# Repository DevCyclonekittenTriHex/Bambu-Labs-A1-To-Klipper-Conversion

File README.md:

## Bambu Lab A1 Klipper Conversion (In development)

## Join Chaz's [**Discord Server**](https://discord.gg/W6B5mBejuC) to help with all bambu labs klipper mods.

> [!Caution]
> Doing any modifications may void your warrenty! 
> [!Caution]
> This Project is in currently not finished, this conversion is done fully at your own risk, I am not liable for any damages done to your machine.

This is constantly being updated, the docs for the conversion will be [Here!](https://devcyclonekittentrihex.github.io/A1K-Documentation/Docs/)

# Aim
The aim of this open source project is to create drop in circuit boards for the Bambu Labs A1 and A1 mini machines; and to provide a good framework to promote modding of these machines. This project will try to intergrate every part from the original printer to make the upgrade seamless. This will give back people privacy and a fully lan or offline system to print.

Currently, I have designed the a1 mainboard and a1/a1m toolhead boards, and am currently going through revisioning.
My target for the pcbs are to order them by November 30th

# Functions

Does work:
- Full hotend heating 
- XYZ Movement
- Stock Part Cooling Fans
- Auto Bed Levelling (with biqu microprobe)
- Filament Runout (with biqu sfs2)

Does not work:
- Heated Bed : Currently have the pinout for it, will be implemented in pcbs.
- Filament Sensor : It is a linear hall sensor, pinout unknown. Will attempt to find.
- AMS Lite : Closed source, other open mmus are compatible
- Display : An unidentified display that is possibly using 4SPI

# Previous Experiments
I previously hooked up an skr pico to the printer, and got it printing without a heated bed. Here is the footage. I also killed my mainboard so there is no more footage.
https://youtu.be/fLf-GMceLxE

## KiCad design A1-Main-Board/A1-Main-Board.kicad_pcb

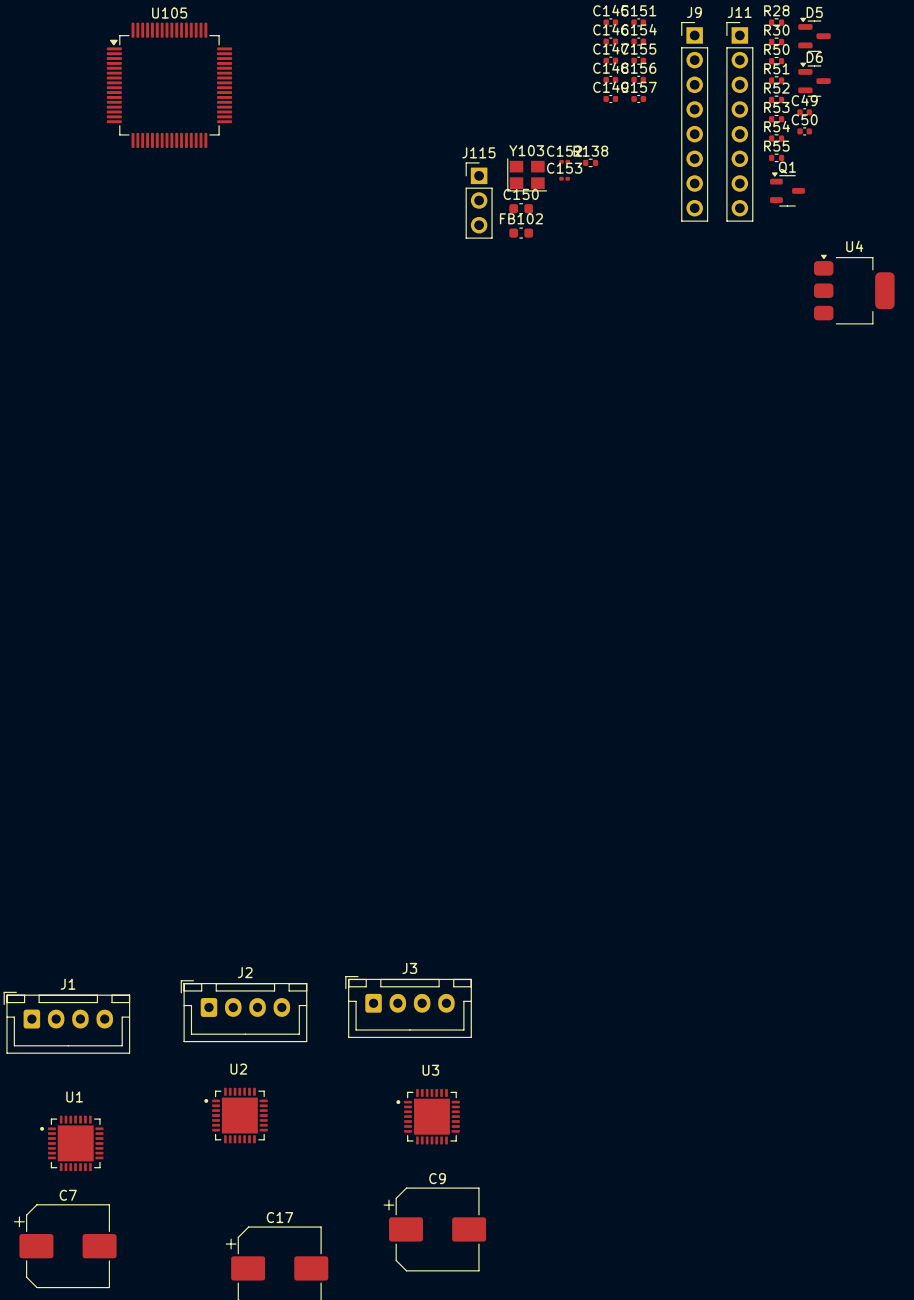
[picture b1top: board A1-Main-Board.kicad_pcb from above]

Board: 2 copper layers, 43 parts (0 on the bottom side), 33 nets, no tracks yet.

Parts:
C7, C9, C17: 100uF; CP_Elec_8x10
C49, C50, C147, C148, C149, C154, C155, C156, C157: 100nF; C_0402_1005Metric
C145, C146: 30pF; C_0402_1005Metric
C150: 10uF; C_0603_1608Metric
C151: 10nF; C_0402_1005Metric
C152, C153: 1uF; C_0201_0603Metric
D5, D6: BAV99; SOT-23
FB102: 120r 100MHz; C_0603_1608Metric
J1, J2, J3: MotorJST; JST_XH_B4B-XH-A_1x04_P2.50mm_Vertical
J9: FPC1; PinHeader_1x08_P2.54mm_Vertical
J11: FPC2; PinHeader_1x08_P2.54mm_Vertical
J115: BOOT; PinHeader_1x03_P2.54mm_Vertical
Q1: NMOS; SOT-23-3
R28: 10R; R_0402_1005Metric
R30: 20kR; R_0402_1005Metric
R50, R53: 4.7kR; R_0402_1005Metric
R51, R52, R54, R55: 2.37kR; R_0402_1005Metric
R138: 10kR; R_0402_1005Metric
U1, U2, U3: TMC2209-LA
U4: AMS1117-3.3; SOT-223-3_TabPin2
U105: STM32G431RBT3; LQFP-64_10x10mm_P0.5mm
Y103: Crystal_GND24; Crystal_SMD_3225-4Pin_3.2x2.5mm

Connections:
+3V3: C147.1, C149.1, C150.1, C153.1, C154.1, C155.1, C156.1, C157.1, FB102.2, J115.1, U1.15 (VCC_IO), U2.9 (MS1_AD0), U2.15 (VCC_IO), U3.10 (MS2_AD1), U3.15 (VCC_IO), U105.1 (VBAT), U105.16 (VDD), U105.32 (VDD), U105.48 (VDD), U105.64 (VDD)
+3V3A: C151.1, C152.1, D5.2 (A), D6.2 (A), FB102.1, R50.1, R53.1, U105.28 (VREF+), U105.29 (VDDA)
+5V: J11.1, U1.8 (5VOUT), U2.8 (5VOUT), U3.8 (5VOUT)
+24V: C7.1, C9.1, C17.1, U1.22 (VS), U1.28 (VS), U2.22 (VS), U2.28 (VS), U3.22 (VS), U3.28 (VS)
/drivers/MA_UART: U1.14 (~PD_UART), U2.14 (~PD_UART), U3.14 (~PD_UART), U105.22 (PC4)
/heated-bed/10k_THB_INP: J11.4, R53.2, R54.1
/heated-bed/100k_THB_INP: J11.2, R50.2, R51.1
/heated-bed/BED_THERM_1: C49.1, R52.2, U105.36 (PB14)
/heated-bed/BED_THERM_2: C50.1, R55.2, U105.43 (PA9)
/heated-bed/HEATED_BED-: J11.7, Q1.1 (D)
/heated-bed/HEATED_BED_PWM: R28.1, R30.1, U105.38 (PC6)
GND: C7.2, C9.2, C17.2, C49.2, C50.2, C145.2, C146.2, C148.2, C151.2, C152.2, C153.2, D5.1 (K), D6.1 (K), J11.3, J11.5, J11.8, J115.3, Q1.3 (S), R30.2, U1.3 (GND), U1.9 (MS1_AD0), U1.10 (MS2_AD1), U1.18 (GND), U1.29 (EXP), U2.3 (GND), U2.10 (MS2_AD1), U2.18 (GND), U2.29 (EXP), U3.3 (GND), U3.9 (MS1_AD0), U3.18 (GND), U3.29 (EXP), U105.15 (VSS), U105.27 (VSSA), U105.31 (VSS), U105.47 (VSS), U105.63 (VSS), Y103.2, Y103.4
unnamed: C147.2, C149.2, C150.2, C154.2, C155.2, C156.2, C157.2
unnamed: D5.3 (K), R51.2, R52.1
unnamed: D6.3 (K), R54.2, R55.1
unnamed: J1.1, U1.24 (OA1)
unnamed: J1.2, U1.26 (OB1)
unnamed: J1.3, U1.21 (OA2)
unnamed: J1.4, U1.1 (OB2)
unnamed: J2.1, U2.24 (OA1)
unnamed: J2.2, U2.26 (OB1)
unnamed: J2.3, U2.21 (OA2)
unnamed: J2.4, U2.1 (OB2)
unnamed: J3.1, U3.24 (OA1)
unnamed: J3.2, U3.26 (OB1)
unnamed: J3.3, U3.21 (OA2)
unnamed: J3.4, U3.1 (OB2)
unnamed: J115.2, R138.1
unnamed: Q1.2 (G), R28.2
unnamed: C148.1, U105.7 (PG10)
unnamed: R138.2, U105.61 (PB8)
unnamed: C145.1, U105.5 (PF0), Y103.1
unnamed: C146.1, U105.6 (PF1), Y103.3

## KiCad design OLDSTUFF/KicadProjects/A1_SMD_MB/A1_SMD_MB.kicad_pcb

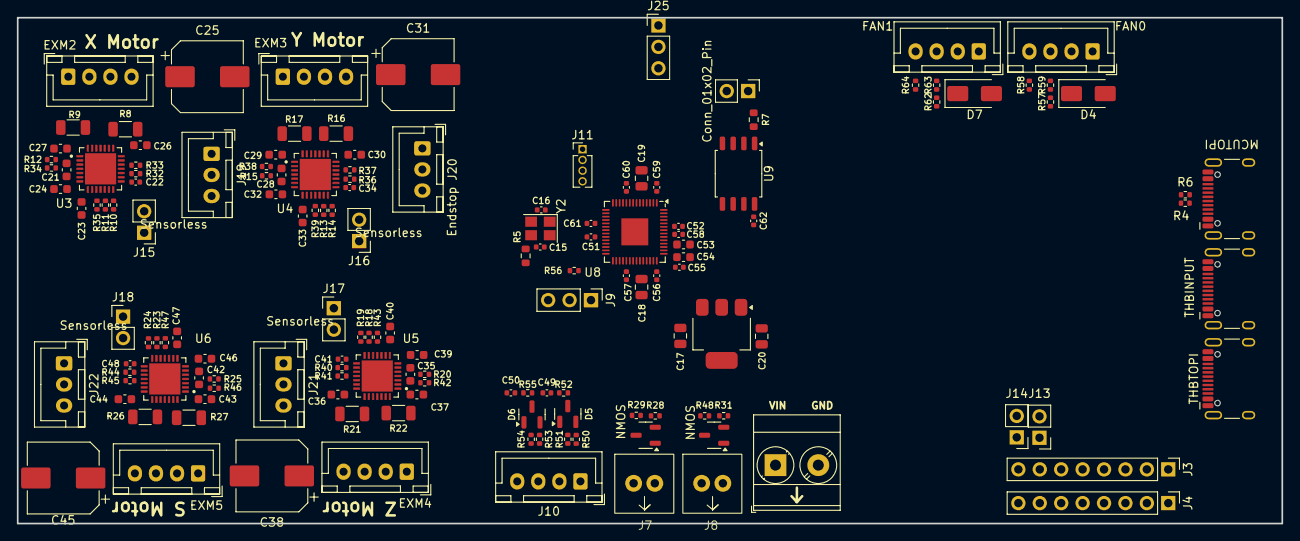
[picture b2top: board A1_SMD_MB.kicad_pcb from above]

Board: 2 copper layers, 150.0 x 60.0 mm, 148 parts (0 on the bottom side), 134 nets, no tracks yet.

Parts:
C15, C16: 15pF; C_0402_1005Metric
C17, C18, C19, C20: 10uF; C_0805_2012Metric
C21, C28, C35, C42: 22nF 50V; C_0603_1608Metric
C22, C34, C41, C48, C49, C50, C51, C52, C55, C56, C57, C58, C59, C60, C61, C62: 100nF; C_0402_1005Metric
C23, C33, C40, C47: 4.7uF; C_0603_1608Metric
C24, C26, C27, C29, C30, C32, C36, C37, C39, C43, C44, C46: 100nF 50V; C_0603_1608Metric
C25, C31, C38, C45: 100uF; CP_Elec_8x10
C53, C54: 1uF; C_0603_1608Metric
D4, D7: D; D_SMA
D5, D6: BAV99; SOT-23
EXM2, EXM3, EXM4, EXM5: Conn_01x04; JST_XH_B4B-XH-A_1x04_P2.50mm_Vertical
J3: FPC2; PinHeader_1x08_P2.54mm_Vertical
J4: FPC1; PinHeader_1x08_P2.54mm_Vertical
J6: FAN0; JST_XH_B4B-XH-A_1x04_P2.50mm_Vertical
J7: HE; ScrewTerminal 7mm x 7mm
J8: HB; ScrewTerminal 7mm x 7mm
J9: Conn_01x03_Pin; PinHeader_1x03_P2.54mm_Vertical
J10: BedTherms; JST_XH_B4B-XH-A_1x04_P2.50mm_Vertical
J11: SWD; PinHeader_1x04_P1.27mm_Vertical
J12: Conn_01x02_Pin; PinHeader_1x02_P2.54mm_Vertical
J13: THM2JMP; PinHeader_1x02_P2.54mm_Vertical
J14: THM1JMP; PinHeader_1x02_P2.54mm_Vertical
J15, J16, J17, J18: Sensorless; PinHeader_1x02_P2.54mm_Vertical
J19, J20, J21, J22: Endstop; JST_XH_B3B-XH-A_1x03_P2.50mm_Vertical
J23: PWR; 1x2 Terminal Block
J24: FAN1; JST_XH_B4B-XH-A_1x04_P2.50mm_Vertical
J25: SPR_IO; PinHeader_1x03_P2.54mm_Vertical
P1: MCUTOPI; USB_C_Receptacle_HCTL_HC-TYPE-C-16P-01A
P2: THBINPUT; USB_C_Receptacle_HCTL_HC-TYPE-C-16P-01A
P3: THBTOPI; USB_C_Receptacle_HCTL_HC-TYPE-C-16P-01A
Q1, Q2: NMOS; SOT-23-3
R4, R6: 27.4o; R_0402_1005Metric
R5: 1k; R_0603_1608Metric
R7: 1ko; R_0603_1608Metric
R8, R9, R16, R17, R21, R22, R26, R27: 100mΩ; R_1206_3216Metric
R10, R11, R12, R13, R14, R15, R18, R19, R20, R23, R24, R25: 20kΩ; R_0402_1005Metric
R28, R31: 10R; R_0402_1005Metric
R29, R48, R58, R64: 20kR; R_0402_1005Metric
R32, R33, R34, R35, R36, R37, R38, R39, R40, R41, R42, R43, R44, R45, R46, R47: 100o; R_0402_1005Metric
R50, R53: 4.7kR; R_0402_1005Metric
R51, R52, R54, R55: 2.37kR; R_0402_1005Metric
R56: 10k; R_0402_1005Metric
R57, R59, R62, R63: 100R; R_0402_1005Metric
U3, U4, U5, U6: TMC2209-LA
U7: NCP1117-1.5_SOT223; SOT-223-3_TabPin2
U8: RP2040; QFN-56-1EP_7x7mm_P0.4mm_EP3.2x3.2mm
U9: W25Q128JVS; SOIC-8_5.3x5.3mm_P1.27mm
Y2: ABM8-272-T3; Crystal_SMD_Abracon_ABM8AIG-4Pin_3.2x2.5mm

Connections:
+1V1: C51.1, C52.1, C53.1, U8.23 (DVDD), U8.45 (VREG_VOUT), U8.50 (DVDD)
+3.3VADC: D5.2 (A), D6.2 (A), R50.1, R53.1
+3V3: C18.1, C19.1, C20.1, C22.2, C34.2, C41.2, C48.2, C54.1, C55.1, C56.1, C57.1, C58.1, C59.1, C60.1, C61.1, C62.1, J3.5, J9.1, J11.1, R12.1, R15.1, R20.1, R25.1, U3.15 (VCC_IO), U4.9 (MS1_AD0), U4.15 (VCC_IO), U5.10 (MS2_AD1), U5.15 (VCC_IO), U6.9 (MS1_AD0), U6.10 (MS2_AD1), U6.15 (VCC_IO), U7.2 (VO), U8.1 (IOVDD), U8.10 (IOVDD), U8.22 (IOVDD), U8.33 (IOVDD), U8.42 (IOVDD), U8.43 (ADC_AVDD), U8.44 (VREG_IN), U8.48 (USB_VDD), U8.49 (IOVDD), U9.8 (VCC)
+5V: C23.2, C33.2, C40.2, C47.2, J3.1, J3.2, J19.3, J20.3, J21.3, J22.3, P2.A8 (SBU1), P2.B8 (SBU2), U3.8 (5VOUT), U4.8 (5VOUT), U5.8 (5VOUT), U6.8 (5VOUT)
+24V: C24.1, C25.1, C26.2, C27.2, C29.2, C30.2, C31.1, C32.1, C36.2, C37.2, C38.1, C39.1, C43.2, C44.2, C45.1, C46.1, D4.2 (A), D7.2 (A), J6.1, J7.1, J8.1, J23.1, J24.1, P2.A4 (VBUS), P2.A9 (VBUS), P2.B4 (VBUS), P2.B9 (VBUS), U3.22 (VS), U3.28 (VS), U4.22 (VS), U4.28 (VS), U5.22 (VS), U5.28 (VS), U6.22 (VS), U6.28 (VS)
/Motors/MS_DIAG: J22.1, R47.2, U8.34 (GPIO22)
/Motors/MS_DIR: R45.1, U8.32 (GPIO21)
/Motors/MS_EN: R46.1, U8.30 (GPIO19)
/Motors/MS_STEP: R44.1, U8.31 (GPIO20)
/Motors/MX_DIAG: J19.1, R35.2, U8.13 (GPIO10)
/Motors/MX_DIR: R33.1, U8.12 (GPIO9)
/Motors/MX_EN: R34.1, U8.9 (GPIO7)
/Motors/MX_STEP: R32.1, U8.11 (GPIO8)
/Motors/MY_DIAG: J20.1, R39.2, U8.17 (GPIO14)
/Motors/MY_DIR: R37.1, U8.16 (GPIO13)
/Motors/MY_EN: R38.1, U8.14 (GPIO11)
/Motors/MY_STEP: R36.1, U8.15 (GPIO12)
/Motors/MZ_DIAG: J21.1, R43.2, U8.29 (GPIO18)
/Motors/MZ_DIR: R41.1, U8.28 (GPIO17)
/Motors/MZ_EN: R42.1, U8.18 (GPIO15)
/Motors/MZ_STEP: R40.1, U8.27 (GPIO16)
/Motors/UART: R10.2, R14.2, R19.2, R24.2, U3.14 (~PD_UART), U4.14 (~PD_UART), U5.14 (~PD_UART), U6.14 (~PD_UART), U8.8 (GPIO6)
/fpc/HB_CT: J3.6, U8.6 (GPIO4)
/fpc/THM1: C50.1, J14.2, R55.2, U8.41 (GPIO29_ADC3)
/fpc/THM2: C49.1, J13.2, R52.2, U8.40 (GPIO28_ADC2)
/mcu/G1: R58.1, U8.3 (GPIO1)
/mcu/G2: R31.1, R48.1, U8.4 (GPIO2)
/mcu/G3: R28.1, R29.1, U8.5 (GPIO3)
/mcu/G23: J25.1, U8.35 (GPIO23)
/mcu/G24: J25.2, U8.36 (GPIO24)
/mcu/G25: J25.3, U8.37 (GPIO25)
/mcu/G26: R62.1, U8.38 (GPIO26_ADC0)
/mcu/G27: R64.1, U8.39 (GPIO27_ADC1)
/mcu/GPIO0: R57.1, U8.2 (GPIO0)
/mcu/IO0: U8.53 (QSPI_SD0), U9.5 (DI/IO_{0})
/mcu/IO1: U8.55 (QSPI_SD1), U9.2 (DO/IO_{1})
/mcu/IO2: U8.54 (QSPI_SD2), U9.3 (~WP/IO_{2})
/mcu/IO3: U8.51 (QSPI_SD3), U9.7 (~HOLD/~RESET/IO_{3})
/mcu/IO_CLK: U8.52 (QSPI_SCLK), U9.6 (CLK)
/mcu/IO_CS: R7.2, U8.56 (QSPI_SS), U9.1 (~CS)
/mcu/USB_D+: P1.A6 (D+), R4.1
/mcu/USB_D-: P1.A7 (D-), R6.1
/mcu/XIN: C16.2, U8.20 (XIN), Y2.1
/mcu/XOUT: R5.2, U8.21 (XOUT)
/stuff/HB_S: Q2.2 (G), R31.2
/stuff/HE_S: Q1.2 (G), R28.2
GND: C22.1, C23.1, C25.2, C26.1, C27.1, C29.1, C30.1, C31.2, C33.1, C34.1, C36.1, C37.1, C38.2, C40.1, C41.1, C43.1, C44.1, C45.2, C47.1, C48.1, C49.2, C50.2, D4.1 (K), D5.1 (K), D6.1 (K), D7.1 (K), J3.3, J3.4, J6.2, J10.2, J10.4, J19.2, J20.2, J21.2, J22.2, J23.2, J24.2, P1.A1 (GND), P1.A12 (GND), P1.B1 (GND), P1.B12 (GND), P1.S1 (SHIELD), P2.A1 (GND), P2.A12 (GND), P2.B1 (GND), P2.B12 (GND), P2.S1 (SHIELD), P3.A1 (GND), P3.A12 (GND), P3.B1 (GND), P3.B12 (GND), P3.S1 (SHIELD), Q1.3 (S), Q2.3 (S), R8.2, R9.2, R10.1, R11.1, R13.1, R14.1, R16.2, R17.2, R18.1, R19.1, R21.2, R22.2, R23.1, R24.1, R26.2, R27.2, R29.2, R48.2, U3.3 (GND), U3.9 (MS1_AD0), U3.10 (MS2_AD1), U3.18 (GND), U3.29 (EXP), U4.3 (GND), U4.10 (MS2_AD1), U4.18 (GND), U4.29 (EXP), U5.3 (GND), U5.9 (MS1_AD0), U5.18 (GND), U5.29 (EXP), U6.3 (GND), U6.18 (GND), U6.29 (EXP)
GND3: C15.1, C16.1, C17.2, C18.2, C19.2, C20.2, C51.2, C52.2, C53.2, C54.2, C55.2, C56.2, C57.2, C58.2, C59.2, C60.2, C61.2, C62.2, J9.3, J11.4, J12.2, U7.1 (GND), U8.19 (TESTEN), U8.57 (GND), U9.4 (GND), Y2.2, Y2.4
unnamed: C15.2, R5.1, Y2.3
unnamed: D5.3 (K), R51.2, R52.1
unnamed: D6.3 (K), R54.2, R55.1
unnamed: EXM2.1, U3.1 (OB2)
unnamed: EXM2.2, U3.26 (OB1)
unnamed: EXM2.3, U3.24 (OA1)
unnamed: EXM2.4, U3.21 (OA2)
unnamed: EXM3.1, U4.1 (OB2)
unnamed: EXM3.2, U4.26 (OB1)
unnamed: EXM3.3, U4.24 (OA1)
unnamed: EXM3.4, U4.21 (OA2)
unnamed: EXM4.1, U5.1 (OB2)
unnamed: EXM4.2, U5.26 (OB1)
unnamed: EXM4.3, U5.24 (OA1)
unnamed: EXM4.4, U5.21 (OA2)
unnamed: EXM5.1, U6.1 (OB2)
unnamed: EXM5.2, U6.26 (OB1)
unnamed: EXM5.3, U6.24 (OA1)
unnamed: EXM5.4, U6.21 (OA2)
unnamed: J6.3, R59.2
unnamed: J6.4, R58.2
unnamed: J7.2, Q1.1 (D)
unnamed: J8.2, Q2.1 (D)
unnamed: J9.2, R56.1
unnamed: J10.1, R50.2, R51.1
unnamed: J10.3, R53.2, R54.1
unnamed: J11.2, U8.24 (SWCLK)
unnamed: J11.3, U8.25 (SWD)
unnamed: J12.1, R7.1
unnamed: J3.7, J13.1
unnamed: J3.8, J14.1
unnamed: J15.1, R35.1
unnamed: J15.2, U3.11 (DIAG)
unnamed: J16.1, R39.1
unnamed: J16.2, U4.11 (DIAG)
unnamed: J17.1, R43.1
unnamed: J17.2, U5.11 (DIAG)
unnamed: J18.1, R47.1
unnamed: J18.2, U6.11 (DIAG)
unnamed: J24.3, R63.2
unnamed: J24.4, R64.2
unnamed: P2.A5 (CC), P2.B5 (VCONN)
unnamed: P2.A6 (D+), P3.A6 (D+)
unnamed: P2.A7 (D-), P3.A7 (D-)
unnamed: R57.2, R59.1
unnamed: R62.2, R63.1
unnamed: R8.1, U3.23 (BRA)
unnamed: R9.1, U3.27 (BRB)
unnamed: R11.2, U3.13 (CLK)
unnamed: C21.1, U3.5 (CPI)
unnamed: C21.2, U3.4 (CPO)
unnamed: R33.2, U3.19 (DIR)
unnamed: R32.2, U3.16 (STEP)
unnamed: C24.2, U3.6 (VCP)
unnamed: R12.2, R34.2, U3.2 (~EN)
unnamed: R16.1, U4.23 (BRA)
unnamed: R17.1, U4.27 (BRB)
unnamed: R13.2, U4.13 (CLK)
unnamed: C28.1, U4.5 (CPI)
unnamed: C28.2, U4.4 (CPO)
unnamed: R37.2, U4.19 (DIR)
unnamed: R36.2, U4.16 (STEP)
unnamed: C32.2, U4.6 (VCP)
unnamed: R15.2, R38.2, U4.2 (~EN)
unnamed: R21.1, U5.23 (BRA)
unnamed: R22.1, U5.27 (BRB)
unnamed: R18.2, U5.13 (CLK)
unnamed: C35.1, U5.5 (CPI)
unnamed: C35.2, U5.4 (CPO)
unnamed: R41.2, U5.19 (DIR)
unnamed: R40.2, U5.16 (STEP)
unnamed: C39.2, U5.6 (VCP)
unnamed: R20.2, R42.2, U5.2 (~EN)
unnamed: R26.1, U6.23 (BRA)
unnamed: R27.1, U6.27 (BRB)
unnamed: R23.2, U6.13 (CLK)
unnamed: C42.1, U6.5 (CPI)
unnamed: C42.2, U6.4 (CPO)
unnamed: R45.2, U6.19 (DIR)
unnamed: R44.2, U6.16 (STEP)
unnamed: C46.2, U6.6 (VCP)
unnamed: R25.2, R46.2, U6.2 (~EN)
unnamed: R56.2, U8.26 (RUN)
unnamed: R6.2, U8.46 (USB_DM)
unnamed: R4.2, U8.47 (USB_DP)
VBUS: C17.1, P1.A4 (VBUS), P1.A9 (VBUS), P1.B4 (VBUS), P1.B9 (VBUS), P3.A4 (VBUS), P3.A9 (VBUS), P3.B4 (VBUS), P3.B9 (VBUS), U7.3 (VI)

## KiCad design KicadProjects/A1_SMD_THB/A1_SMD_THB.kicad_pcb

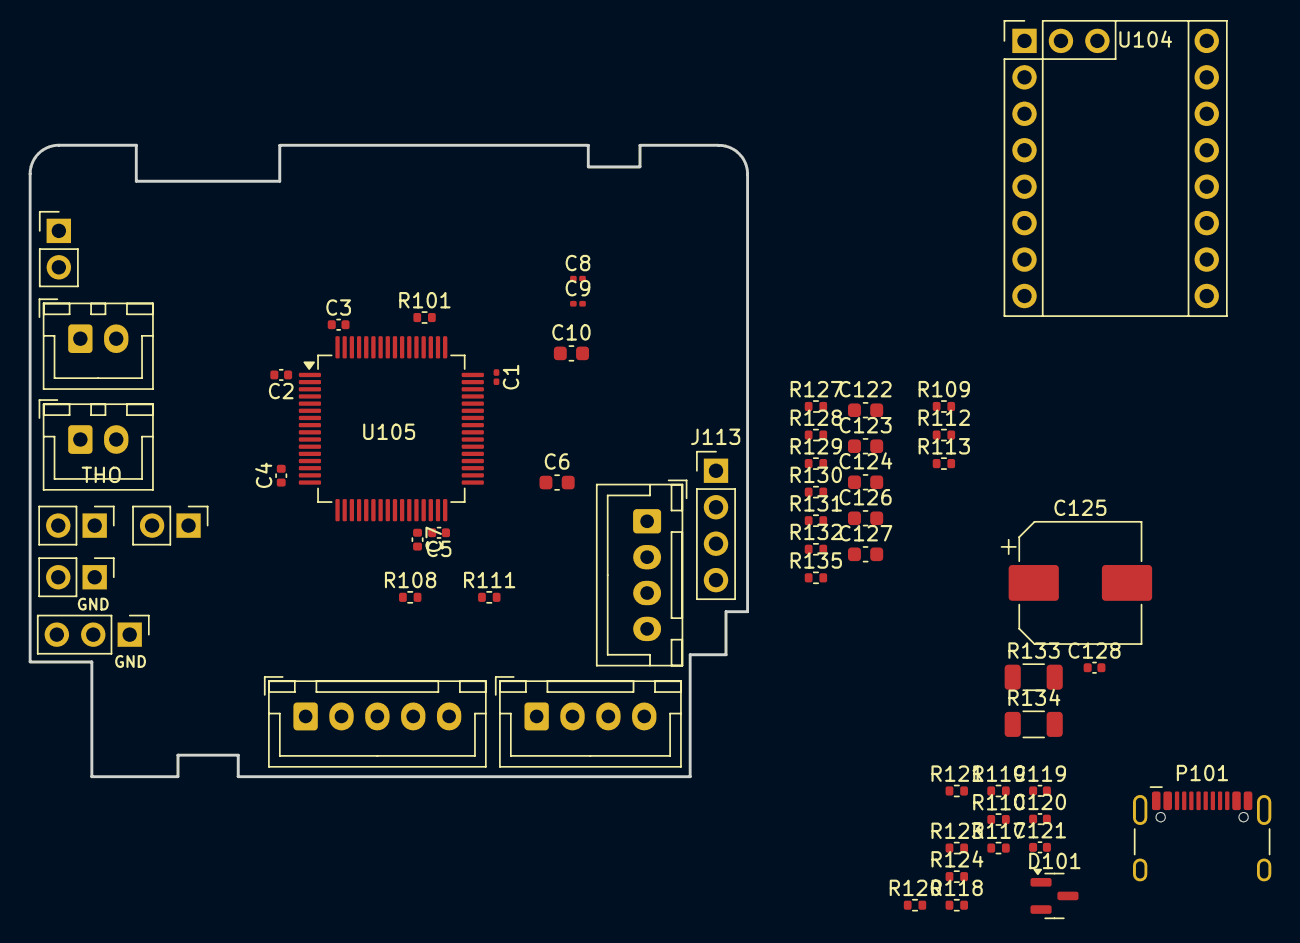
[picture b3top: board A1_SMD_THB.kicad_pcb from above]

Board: 2 copper layers, 50.0 x 44.0 mm, 58 parts (0 on the bottom side), 46 nets, no tracks yet.

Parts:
C1: 10uF; C_0201_0603Metric
C2, C3, C4, C5, C119, C120, C121, C128: 100nF; C_0402_1005Metric
C6, C10: 10uF; C_0603_1608Metric
C7: 10nF; C_0402_1005Metric
C8, C9: 1uF; C_0201_0603Metric
C122: 22nF 50V; C_0603_1608Metric
C123, C124, C126: 100nF 50V; C_0603_1608Metric
C125: 100uF; CP_Elec_8x10
C127: 4.7uF; C_0603_1608Metric
D101: BAV99; SOT-23
EXM101: Conn_01x04; JST_XH_B4B-XH-A_1x04_P2.50mm_Vertical
J1: Conn_01x02_Pin; PinHeader_1x02_P2.54mm_Vertical
J104: THO; JST_XH_B2B-XH-A_1x02_P2.50mm_Vertical
J105: F_SR2; PinHeader_1x02_P2.54mm_Vertical
J106: F_SR1; PinHeader_1x02_P2.54mm_Vertical
J107: EXF; JST_XH_B5B-XH-A_1x05_P2.50mm_Vertical
J108: HE; JST_XH_B2B-XH-A_1x02_P2.50mm_Vertical
J109: PCF_FAN; JST_XH_B4B-XH-A_1x04_P2.50mm_Vertical
J111: BL_PROBE; PinHeader_1x02_P2.54mm_Vertical
J112: BL_SERVO; PinHeader_1x03_P2.54mm_Vertical
J113: ADXL345; PinHeader_1x04_P2.54mm_Vertical
P101: USB_C_Plug; USB_C_Receptacle_HCTL_HC-TYPE-C-16P-01A
R101: 1k; R_0402_1005Metric
R108, R109, R119, R124: 100; R_0402_1005Metric
R110: 4.7kR; R_0402_1005Metric
R111, R117: 2.37kR; R_0402_1005Metric
R112, R113: 20k; R_0402_1005Metric
R118, R123: 10k; R_0402_1005Metric
R120: 10R; R_0402_1005Metric
R121: 20kR; R_0402_1005Metric
R127, R128, R129: 20kΩ; R_0402_1005Metric
R130, R131, R132, R135: 100o; R_0402_1005Metric
R133, R134: 100mΩ; R_1206_3216Metric
U104: TMC2209-LA; TMC2209 Footprint
U105: STM32G474RBTx; LQFP-64_10x10mm_P0.5mm

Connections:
3V3: C128.2, U104.15 (VCC_IO)
+3.3VADC: D101.2 (A), R110.1
+3V3: C1.1, C2.1, C3.1, C4.1, C5.1, C6.1, C9.1, C10.2, J112.2, J113.1, R129.1, U105.1 (VBAT), U105.16 (VDD), U105.32 (VDD), U105.48 (VDD), U105.64 (VDD)
+3V3A: C7.1, C8.1, U105.29 (VDDA)
+5V: C127.2, U104.8 (5VOUT)
+24V: C123.2, C124.2, C125.1, C126.1, J107.2, J108.1, J109.1, P101.A4 (VBUS), P101.A9 (VBUS), P101.B4 (VBUS), P101.B9 (VBUS)
/accelerometer/SCL: J113.4, U105.51 (PA15)
/accelerometer/SDA: J113.3, U105.60 (PB7)
/mainio/BL_PROBE: J111.2, U105.42 (PA8)
/mainio/BL_SERVO: J112.3, U105.41 (PC9)
/mainio/EXF_PWM: R119.1, U105.35 (PB13)
/mainio/EXF_TACH: R118.1, U105.38 (PC6)
/mainio/FIL_SNS1: R108.1, U105.23 (PC5)
/mainio/FIL_SNS2: R109.1, U105.22 (PC4)
/mainio/HE_SIG: R120.1, R120.2, R121.1, U105.34 (PB12)
/mainio/PCF_PWM: R124.1, U105.36 (PB14)
/mainio/PCF_TACH: R123.1, U105.39 (PC7)
/mainio/THO: C121.1, R117.2, U105.21 (PA7)
/mcu_stm32/MT_DIAG: R135.2, U105.58 (PB5)
/mcu_stm32/MT_DIR: R131.1, U105.57 (PB4)
/mcu_stm32/MT_ENABLE: R132.1, U105.54 (PC12)
/mcu_stm32/MT_STEP: R130.1, U105.55 (PD2)
/mcu_stm32/MT_UART_RX: R101.1, U105.53 (PC11)
/mcu_stm32/MT_UART_TX: R101.2, R128.2, U104.14 (~PD_UART), U105.52 (PC10)
GND: C1.2, C2.2, C3.2, C4.2, C5.2, C6.2, C7.2, C8.2, C9.2, C10.1, C121.2, C123.1, C124.1, C125.2, C127.1, C128.1, D101.1 (K), J104.2, J105.1, J107.3, J109.2, J113.2, P101.A1 (GND), P101.A12 (GND), P101.B1 (GND), P101.B12 (GND), P101.S1 (SHIELD), R121.2, R127.1, R128.1, R133.2, R134.2, U104.3 (GND), U104.9 (MS1_AD0), U104.10 (MS2_AD1), U104.18 (GND), U105.15 (VSS), U105.27 (VSSA), U105.31 (VSS), U105.47 (VSS), U105.63 (VSS)
GND3: C119.2, C120.2, J1.2, J111.1, J112.1
unnamed: C119.1, R108.2, R112.1
unnamed: C120.1, R109.2, R113.1
unnamed: D101.3 (K), R111.2, R117.1
unnamed: EXM101.1, U104.1 (OB2)
unnamed: J104.1, R110.2, R111.1
unnamed: J105.2, R113.2
unnamed: J106.2, R112.2
unnamed: J107.4, R119.2
unnamed: J107.5, R118.2
unnamed: J109.3, R124.2
unnamed: J109.4, R123.2
unnamed: P101.A5 (CC), P101.B5 (VCONN)
unnamed: R127.2, U104.13 (CLK)
unnamed: C122.1, U104.5 (CPI)
unnamed: C122.2, U104.4 (CPO)
unnamed: R135.1, U104.11 (DIAG)
unnamed: R130.2, U104.16 (STEP)
unnamed: C126.2, U104.6 (VCP)
unnamed: R129.2, R132.2, U104.2 (~EN)
VBUS: P101.A8 (SBU1), P101.B8 (SBU2)

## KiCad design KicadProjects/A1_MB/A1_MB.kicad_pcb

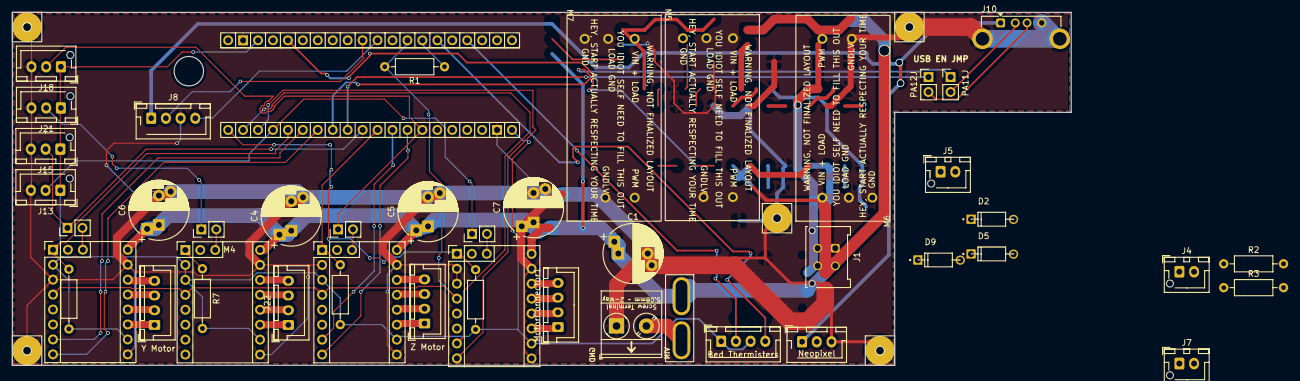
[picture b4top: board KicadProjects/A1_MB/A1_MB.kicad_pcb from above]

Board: 2 copper layers, 180.0 x 60.0 mm, 52 parts (0 on the bottom side), 51 nets.

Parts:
C1, C4, C5, C6, C7: 220uF; CP_Radial_D10.0mm_P5.00mm_P7.50mm
D2, D5, D9: D; Diode
F1: Mini ATO Fuse; Updated ATO Mini-Blade_2Post
H1, H2, H3, H4, H5: M1.5; Mountinghole_m1.5
J1: Molex 2x02 Microfit; Molex_Micro-Fit_3.0_43045-0412_2x02_P3.00mm_Vertical
J3: Neopixel; JST_XH_B3B-XH-AM_1x03_P2.50mm_Vertical
J4: HeatedBedConn; JST_XH_B2B-XH-AM_1x02_P2.50mm_Vertical
J5: HotendConn; JST_XH_B2B-XH-AM_1x02_P2.50mm_Vertical
J7: FanConn; JST_XH_B2B-XH-AM_1x02_P2.50mm_Vertical
J8: SmFilSns; JST_XH_B4B-XH-AM_1x04_P2.50mm_Vertical
J9: Screw_Terminal_01x02; 1x2 Terminal Block
J10: USB_A; USB_A_Connfly_DS1095
J11: Bed Thermisters; JST_XH_B4B-XH-A_1x04_P2.50mm_Vertical
J12, J14#2, J17, J20: SensorlessHoming; PinHeader_1x02_P2.54mm_Vertical
J13, J15#2, J18, J21: Endstop; JST_XH_B3B-XH-AM_1x03_P2.50mm_Vertical
J14: PA11J; PinHeader_1x02_P2.54mm_Vertical
J15: PA12J; PinHeader_1x02_P2.54mm_Vertical
J16, J19, J22: Conn_01x04; JST_XH_B4B-XH-A_1x04_P2.50mm_Vertical
M1, M2, M3, M4: TMC2209 Breakout; TMC2209 Footprint
M5, M6, M7: MosfetModule
MotorConnector1: Conn_01x04; JST_XH_B4B-XH-A_1x04_P2.50mm_Vertical
R1: 1kΩ; R_Axial_DIN0207_L6.3mm_D2.5mm_P10.16mm_Horizontal
R2, R3: 4.7kΩ; R_Axial_DIN0207_L6.3mm_D2.5mm_P10.16mm_Horizontal
R4, R5, R6, R7: 10kΩ; R_Axial_DIN0207_L6.3mm_D2.5mm_P10.16mm_Horizontal
U1: STM32 Blackpill Socketed

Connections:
+3V3: J13.1, J15#2.1, J18.1, J21.1, M1.10 (VDD), M2.2 (MS1), M2.10 (VDD), M3.3 (MS2), M3.10 (VDD), M4.2 (MS1), M4.3 (MS2), M4.10 (VDD), R2.1, R3.1, R4.2, R5.2, R6.2, R7.2, U1.18 (3V3), U1.40 (3V3)
+5V: J3.1, J8.1, J10.1 (VBUS)
+24V: C1.1, C4.1, C5.1, C6.1, C7.1, D2.1 (K), D5.1 (K), D9.1 (K), F1.1, J1.1, J1.4, J4.1, J5.1, J7.1, M1.16 (VM), M2.16 (VM), M3.16 (VM), M4.16 (VM)
/BED_THM_1: J11.2, R2.2, U1.6 (PA0)
/BED_THM_2: J11.4, R3.2, U1.4 (PC15)
/EMotor/A1: J22.3, M4.13 (A1)
/EMotor/A2: J22.4, M4.14 (A2)
/EMotor/B1: J22.2, M4.12 (B1)
/EMotor/B2: J22.1, M4.11 (B2)
/ME_DIAG: J20.1, J21.2
/ME_EN: M4.1 (ENABLE), R7.1
/MX_DIAG: J12.1, J13.2, U1.24 (PB15)
/MX_DIR: M1.8 (DIR), U1.23 (PB14)
/MX_EN: M1.1 (ENABLE), R4.1, U1.21 (PB12)
/MX_STEP: M1.7 (STEP), U1.22 (PB13)
/MY_DIAG: J14#2.1, J15#2.2, U1.30 (PA15)
/MY_DIR: M2.8 (DIR), U1.27 (PA10)
/MY_EN: M2.1 (ENABLE), R5.1, U1.25 (PA8)
/MY_STEP: M2.7 (STEP), U1.26 (PA9)
/MZ_DIAG: J17.1, J18.2, U1.34 (PB6)
/MZ_DIR: M3.8 (DIR), U1.33 (PB5)
/MZ_EN: M3.1 (ENABLE), R6.1, U1.31 (PB3)
/MZ_STEP: M3.7 (STEP), U1.32 (PB4)
/M_UART: M1.4 (PDN1), M2.4 (PDN1), M3.4 (PDN1), M4.4 (PDN1), R1.2, U1.8 (PA2)
/Mosfet1/Output_Return: D5.2 (A), J4.2
/Mosfet2/Output_Return: D2.2 (A), J1.3, J5.2
/Mosfet3/Output_Return: D9.2 (A), J7.2
/OpticSensor: J8.4, U1.10 (PA4)
/PA11: J14.1, U1.28 (PA11)
/PA12: J15.1, U1.29 (PA12)
/SwitchSensor: J8.2, U1.11 (PA5)
/UART_RX: R1.1, U1.7 (PA1)
/XMotor/A1: M1.13 (A1), MotorConnector1.3
/XMotor/A2: M1.14 (A2), MotorConnector1.4
/XMotor/B1: M1.12 (B1), MotorConnector1.2
/XMotor/B2: M1.11 (B2), MotorConnector1.1
/YMotor/A1: J16.3, M2.13 (A1)
/YMotor/A2: J16.4, M2.14 (A2)
/YMotor/B1: J16.2, M2.12 (B1)
/YMotor/B2: J16.1, M2.11 (B2)
/ZMotor/A1: J19.3, M3.13 (A1)
/ZMotor/A2: J19.4, M3.14 (A2)
/ZMotor/B1: J19.2, M3.12 (B1)
/ZMotor/B2: J19.1, M3.11 (B2)
GND: C1.2, C4.2, C5.2, C6.2, C7.2, H1.1, H2.1, H3.1, H4.1, H5.1, J1.2, J3.3, J8.3, J9.1, J10.4 (GND), J10.5 (Shield), J13.3, J15#2.3, J18.3, J21.3, M1.9 (GND), M1.15 (GND), M2.9 (GND), M2.15 (GND), M3.9 (GND), M3.15 (GND), M4.9 (GND), M4.15 (GND), U1.19 (GND), U1.39 (GND)
GNDA: J11.1, J11.3, M1.2 (MS1), M1.3 (MS2), M2.3 (MS2), M3.2 (MS1)
unnamed: F1.2, J9.2
unnamed: J12.2, M1.18 (DIAG)
unnamed: J14#2.2, M2.18 (DIAG)
unnamed: J17.2, M3.18 (DIAG)
unnamed: J20.2, M4.18 (DIAG)

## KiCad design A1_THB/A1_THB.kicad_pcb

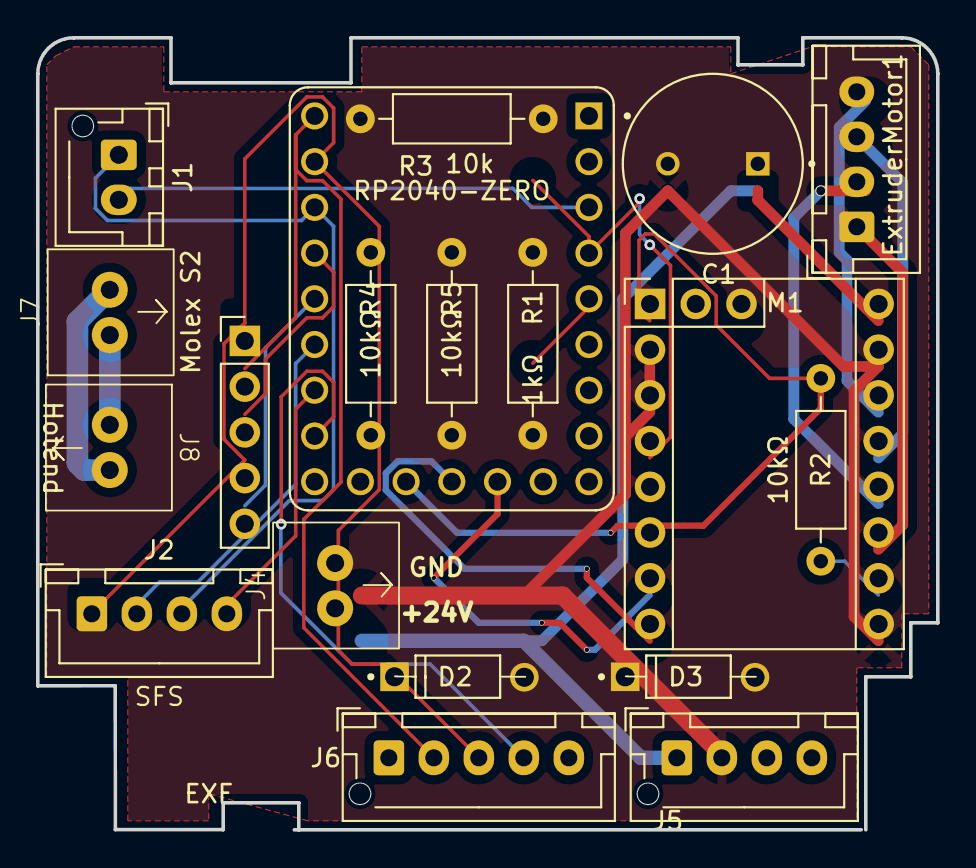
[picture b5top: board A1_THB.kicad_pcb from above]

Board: 2 copper layers, 50.0 x 44.0 mm, 19 parts (0 on the bottom side), 24 nets.

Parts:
C1: 100uF 63V; Cap63V100UF
D2, D3: D; DIOAD1036W78L470D235
ExtruderMotor1: Conn_01x04; JST_XH_B4B-XH-A_1x04_P2.50mm_Vertical
J1: Conn_01x02; JST_XH_B2B-XH-AM_1x02_P2.50mm_Vertical
J2: SFS; JST_XH_B4B-XH-A_1x04_P2.50mm_Vertical
J3: Probe; PinHeader_1x05_P2.54mm_Vertical
J4: MolexS1; ScrewTerminal 7mm x 7mm
J5: PCF; JST_XH_B4B-XH-AM_1x04_P2.50mm_Vertical
J6: EXF; JST_XH_B5B-XH-AM_1x05_P2.50mm_Vertical
J7: Molex S2; ScrewTerminal 7mm x 7mm
J8: Hotend; ScrewTerminal 7mm x 7mm
M1: StepperMotor; TMC2209 Footprint
R1: 1kΩ; R_Axial_DIN0207_L6.3mm_D2.5mm_P10.16mm_Horizontal
R2, R4, R5: 10kΩ; R_Axial_DIN0207_L6.3mm_D2.5mm_P10.16mm_Horizontal
R3: 10k; R_Axial_DIN0207_L6.3mm_D2.5mm_P10.16mm_Horizontal
U1: RP2040-ZERO

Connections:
+3V3: M1.10 (VDD), R2.2, U1.21 (3V3)
+5V: D2.1 (K), J3.2, J6.2, U1.23 (5V)
+24V: C1.1, D3.1 (K), J4.1, J5.1, M1.16 (VM)
/3V3: J1.1, J2.3
/BL_PR: J3.5, U1.19 (GP28)
/BL_SV: J3.3, U1.20 (GP29)
/EXF_SG: J6.4, U1.16 (GP15)
/ExtruderDriver/A1: ExtruderMotor1.3, M1.13 (A1)
/ExtruderDriver/A2: ExtruderMotor1.4, M1.14 (A2)
/ExtruderDriver/B1: ExtruderMotor1.2, M1.12 (B1)
/ExtruderDriver/B2: ExtruderMotor1.1, M1.11 (B2)
/ExtruderDriver/ENABLE: M1.1 (ENABLE), R2.1
/GND_LV: J2.1, R3.2
/M_UART: M1.4 (PDN1), R1.1, U1.4 (GP3)
/PCF_SG: J5.3, U1.15 (GP14)
/SFS_ENC: J2.2, U1.18 (GP27)
/SFS_SW: J2.4, U1.17 (GP26)
/TH_SG: J1.2, R3.1
GND: C1.2, D2.2 (A), D3.2 (A), J3.1, J3.4, J4.2, J5.2, J6.3, M1.2 (MS1), M1.3 (MS2), M1.9 (GND), M1.15 (GND), U1.22 (GND)
unnamed: J5.4, R5.1
unnamed: J6.5, R4.1
unnamed: J7.1, J8.1
unnamed: J7.2, J8.2
unnamed: R1.2, U1.5 (GP4)

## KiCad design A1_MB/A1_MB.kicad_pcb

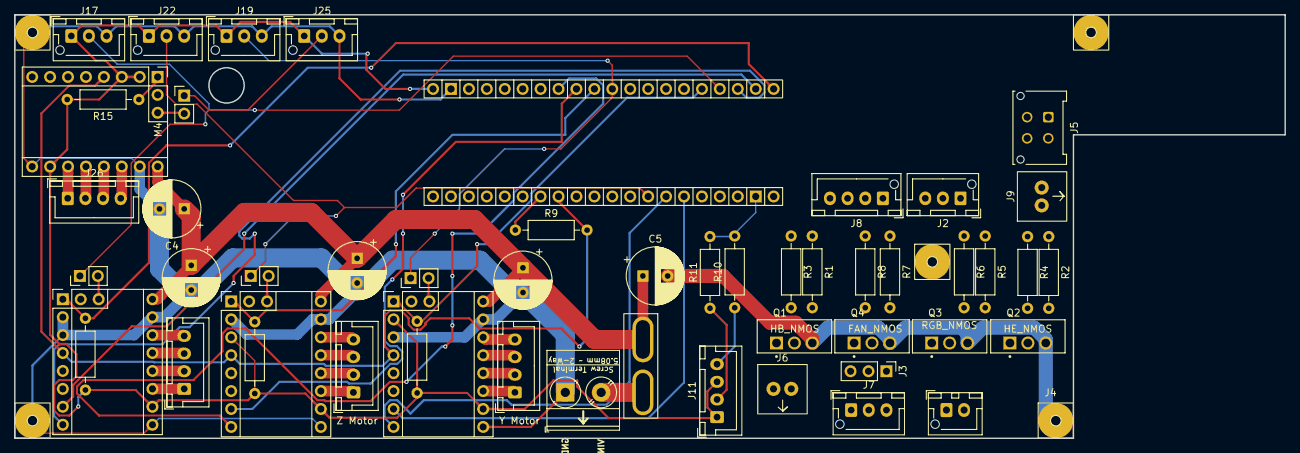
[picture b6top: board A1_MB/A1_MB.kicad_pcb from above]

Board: 2 copper layers, 180.0 x 60.0 mm, 57 parts (0 on the bottom side), 60 nets.

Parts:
C1, C2, C3, C4, C5: 220uF; CP_Radial_D8.0mm_P3.50mm
F1: Mini ATO Fuse; Updated ATO Mini-Blade_2Post
H1, H2, H3, H4, H5: M1.5; Mountinghole_m1.5
J2: Neopixel; JST_XH_B3B-XH-AM_1x03_P2.50mm_Vertical
J3: FAN0_VS; PinHeader_1x03_P2.54mm_Vertical
J4: RGB_2PIN; JST_XH_B2B-XH-AM_1x02_P2.50mm_Vertical
J5: Molex 2x02 Microfit; Molex_Micro-Fit_3.0_43045-0412_2x02_P3.00mm_Vertical
J6: HeatedBed; ScrewTerminal 7mm x 7mm
J7: FAN0; JST_XH_B3B-XH-AM_1x03_P2.50mm_Vertical
J8: SFS; JST_XH_B4B-XH-AM_1x04_P2.50mm_Vertical
J9: Hotend; ScrewTerminal 7mm x 7mm
J10: Screw_Terminal_01x02; 1x2 Terminal Block
J11: Bed Thermisters; JST_XH_B4B-XH-A_1x04_P2.50mm_Vertical
J16, J18, J21, J24: SensorlessHoming; PinHeader_1x02_P2.54mm_Vertical
J17, J19, J22, J25: Endstop; JST_XH_B3B-XH-AM_1x03_P2.50mm_Vertical
J20, J23, J26: Conn_01x04; JST_XH_B4B-XH-A_1x04_P2.50mm_Vertical
M1, M2, M3, M4: TMC2209 Breakout; TMC2209 Footprint
MotorConnector1: Conn_01x04; JST_XH_B4B-XH-A_1x04_P2.50mm_Vertical
Q1: HB_NMOS; TO254P1054X469X1930-3
Q2: HE_NMOS; TO254P1054X469X1930-3
Q3: RGB_NMOS; TO254P1054X469X1930-3
Q4: FAN_NMOS; TO254P1054X469X1930-3
R1, R2, R5, R7: 100k; R_Axial_DIN0207_L6.3mm_D2.5mm_P10.16mm_Horizontal
R3, R4, R6, R8: 1k; R_Axial_DIN0207_L6.3mm_D2.5mm_P10.16mm_Horizontal
R9: 1kΩ; R_Axial_DIN0207_L6.3mm_D2.5mm_P10.16mm_Horizontal
R10, R11: 10k; R_Axial_DIN0207_L6.3mm_D2.5mm_P10.16mm_Horizontal
R12, R13, R14, R15: 10kΩ; R_Axial_DIN0207_L6.3mm_D2.5mm_P10.16mm_Horizontal
U1: STM32 Blackpill Socketed

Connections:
3V3: J7.3, Q4.1 (D)
24V: J5.1, J5.4, J6.1, J9.1
+3V3: J11.1, J11.3, J17.1, J19.1, J22.1, J25.1, M1.10 (VDD), M2.2 (MS1), M2.10 (VDD), M3.3 (MS2), M3.10 (VDD), M4.2 (MS1), M4.3 (MS2), M4.10 (VDD), R12.2, R13.2, R14.2, R15.2, U1.18 (3V3), U1.40 (3V3)
+5V: J2.1, J3.1, J4.1, J8.1
+24V: C1.1, C2.1, C3.1, C4.1, C5.1, F1.1, J3.3, M1.16 (VM), M2.16 (VM), M3.16 (VM), M4.16 (VM)
/ HEATED_BED_PIN: R1.1, R3.1
/BED_THM_1: J11.4, R10.1, U1.6 (PA0)
/BED_THM_2: J11.2, R11.1, U1.4 (PC15)
/EMotor/A1: J26.3, M4.13 (A1)
/EMotor/A2: J26.4, M4.14 (A2)
/EMotor/B1: J26.2, M4.12 (B1)
/EMotor/B2: J26.1, M4.11 (B2)
/FAN0_PIN: R7.1, R8.1, U1.27 (PA10)
/HEATED_BED_RETURN: J6.2, Q1.1 (D)
/HEATER_PIN: R2.1, R4.1, U1.34 (PB6)
/HEATER_RETURN: J5.3, J9.2, Q2.1 (D)
/ME_DIAG: J24.1, J25.2
/ME_EN: M4.1 (ENABLE), R15.1
/MX_DIAG: J16.1, J17.2, U1.24 (PB15)
/MX_DIR: M1.8 (DIR), U1.23 (PB14)
/MX_EN: M1.1 (ENABLE), R12.1, U1.21 (PB12)
/MX_STEP: M1.7 (STEP), U1.22 (PB13)
/MY_DIAG: J18.1, J19.2, U1.30 (PA15)
/MY_DIR: M2.8 (DIR), U1.14 (PB0)
/MY_EN: M2.1 (ENABLE), R13.1, U1.25 (PA8)
/MY_STEP: M2.7 (STEP), U1.15 (PB1)
/MZ_DIAG: J21.1, J22.2, U1.13 (PA7)
/MZ_DIR: M3.8 (DIR), U1.33 (PB5)
/MZ_EN: M3.1 (ENABLE), R14.1, U1.31 (PB3)
/MZ_STEP: M3.7 (STEP), U1.32 (PB4)
/M_UART: M1.4 (PDN1), M2.4 (PDN1), M3.4 (PDN1), M4.4 (PDN1), R9.2, U1.8 (PA2)
/NEOPIXEL_PIN: J2.2, U1.26 (PA9)
/OpticSensor: J8.4, U1.10 (PA4)
/RGB_PIN: R5.1, R6.1, U1.16 (PB2)
/SwitchSensor: J8.2, U1.11 (PA5)
/UART_RX: R9.1, U1.7 (PA1)
/XMotor/A1: M1.13 (A1), MotorConnector1.3
/XMotor/A2: M1.14 (A2), MotorConnector1.4
/XMotor/B1: M1.12 (B1), MotorConnector1.2
/XMotor/B2: M1.11 (B2), MotorConnector1.1
/YMotor/A1: J20.3, M2.13 (A1)
/YMotor/A2: J20.4, M2.14 (A2)
/YMotor/B1: J20.2, M2.12 (B1)
/YMotor/B2: J20.1, M2.11 (B2)
/ZMotor/A1: J23.3, M3.13 (A1)
/ZMotor/A2: J23.4, M3.14 (A2)
/ZMotor/B1: J23.2, M3.12 (B1)
/ZMotor/B2: J23.1, M3.11 (B2)
GND: C1.2, C2.2, C3.2, C4.2, C5.2, H1.1, H2.1, H3.1, H4.1, H5.1, J2.3, J5.2, J7.2, J8.3, J10.1, J17.3, J19.3, J22.3, J25.3, M1.2 (MS1), M1.3 (MS2), M1.9 (GND), M1.15 (GND), M2.3 (MS2), M2.9 (GND), M2.15 (GND), M3.2 (MS1), M3.9 (GND), M3.15 (GND), M4.9 (GND), M4.15 (GND), Q1.3 (S), Q2.3 (S), Q3.3 (S), Q4.3 (S), R1.2, R2.2, R5.2, R7.2, R10.2, R11.2, U1.19 (GND), U1.39 (GND)
unnamed: J3.2, J7.1
unnamed: J4.2, Q3.1 (D)
unnamed: F1.2, J10.2
unnamed: J16.2, M1.18 (DIAG)
unnamed: J18.2, M2.18 (DIAG)
unnamed: J21.2, M3.18 (DIAG)
unnamed: J24.2, M4.18 (DIAG)
unnamed: Q1.2 (G), R3.2
unnamed: Q2.2 (G), R4.2
unnamed: Q3.2 (G), R6.2
unnamed: Q4.2 (G), R8.2
